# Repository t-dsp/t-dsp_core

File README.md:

# T-DSP Core

**Part of the [T-DSP](https://t-dsp.com) open modular audio platform.**

A compact 4-layer digital backplane for the T-DSP modular ecosystem. Hosts a Teensy 4.1 and ESP32 with USB Audio, MIDI, Ethernet, and TDM expansion headers for connecting T-DSP audio modules.

| | |
|:---:|:---:|
|  |  |
|  |  |

**[View 3D Render Gallery](https://t-dsp.github.io/t-dsp_core/gallery.html)** -- interactive slideshow of all board views

## About T-DSP

T-DSP is an open modular audio platform designed for musicians, engineers, and developers who want powerful digital signal processing in a flexible, hackable format. Built around the [Teensy](https://www.pjrc.com/teensy/) microcontroller and the [Teensy Audio Library](https://www.pjrc.com/teensy/td_libs_Audio.html), T-DSP combines studio-quality audio with a growing library of open-source modules.

Learn more at [t-dsp.com](https://t-dsp.com).

## Overview

The T-DSP Core is a **4-layer digital backplane PCB** hosting a Teensy 4.1 and ESP32 alongside supporting ICs. It provides USB Audio, MIDI, Ethernet, and TDM expansion headers for connecting T-DSP audio modules -- in a more accessible and cost-effective form factor than the 8-layer Desktop Pro.

## Processing

- **Teensy 4.1** -- ARM Cortex-M7 running the Teensy Audio Library for real-time DSP (mixing, effects, synthesis, routing). Also receives USB Audio.
- **ESP32** -- UI controller, WiFi/Bluetooth. Drives the display, buttons, and encoder, and sends commands to the Teensy over serial.

## Connectivity

### Audio I/O
- **3.5mm headphone jack** -- Switchcraft 35RAPC4BV4
- **RCA outputs** -- Stereo analog audio output
- **S/PDIF** -- Digital audio input and output

### USB
- **USB-C DEVICE** -- Power and USB Audio to Teensy with ESD protection
- **USB-A HOST** -- USB host connector

### Networking
- **RJ45 Ethernet** -- Wired network connectivity

### MIDI
- **MIDI input** -- 3.5mm TRS with optical isolation (H11L1)
- **MIDI GPIO** -- Configurable for MIDI in, out, or thru

### Power
- **Dual power input** -- USB-C or external supply via JST-XH header, with TPS22860 power switch for automatic switchover
- **Reverse polarity protection** -- P-channel MOSFET on power inputs
- **Power indicators** -- LED indicators for 5V and 12V rails

### Storage
- **SD card** -- Accessible via Teensy 4.1 built-in SD slot

## Expansion

- **2x TDM expansion headers** (2x10 pin, 2.54mm) -- Connect T-DSP audio modules
  - TDM digital audio bus (BCLK, LRCK, DATA_IN, DATA_OUT, MCLK)
  - I2C control bus (SDA, SCL)
  - Power rails (3.3V, 5V, 12V, GND)
  - Control pins (Held-high, Held-low)
- Modules can be soldered directly or socketed with pin headers
- Multiple modules can be chained on the same TDM bus

## User Interface

- **GPIO header** -- Active-low buttons, rotary encoder, and display connections for tactile UI
- **OLED display header** (128x64, SSD1306) -- Status and menu-driven UI
- **3.2" TFT touchscreen header** (ILI9341) -- Touchscreen UI
- **SK6812 addressable LED header** -- ESP32 and Teensy status indication, plus LED strip control

## Board Design

- **4-layer PCB** -- F.Cu (components/analog), In1.Cu (ground plane), In2.Cu (signal/digital), B.Cu (components/analog)
- **1.6mm board thickness**
- LDO voltage regulation for clean analog power
- Separate analog and digital ground domains
- Buffered digital outputs for reliable module distribution

## Project Files

| Directory | Contents |
|-----------|----------|
| `/3d_models/` | 3D models for PCB components |
| `/documentation/` | Schematic PDF, board images, and reference docs |
| `/lib_fp/` | Custom KiCad footprint libraries |
| `/lib_sch/` | Custom KiCad schematic symbol libraries |
| `/manufacturing/` | CI-generated manufacturing outputs (gerbers, BOM, pick & place) |
| `/panel/` | Panelized board layouts for production |

## Status

This board is under active development.

If you build one, we'd love to hear how it goes -- please open an issue or reach out with your findings.

## Contact

For consulting, custom board design, or commercial licensing inquiries, reach out via [LinkedIn](https://linkedin.com/in/jayshoe).

## License

This project is licensed under the [Creative Commons Attribution-NonCommercial-ShareAlike 4.0 International (CC BY-NC-SA 4.0)](https://creativecommons.org/licenses/by-nc-sa/4.0/).

You are free to share and adapt this work for non-commercial purposes, as long as you give appropriate credit and distribute any derivatives under the same license.

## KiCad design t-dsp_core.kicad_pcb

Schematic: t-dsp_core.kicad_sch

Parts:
C1, C29, C30: 1 uF; C_0603_1608Metric; LCSC C15849
C2, C3, C4, C5, C16, C17, C21, C22, C32, C35, C40: 0.1 uF; C_0603_1608Metric; LCSC C14663
C12, C23, C31, C33, C34, C44: 10 uF; C_0603_1608Metric; LCSC C19702
C15: 100 uF; C_1206_3216Metric_Pad1.33x1.80mm_HandSolder; LCSC C15008
C18, C19, C131, C133, C140, C141, C142, C143, C150, C153: 100nF; C_0603_1608Metric; LCSC C14663
C27, C28: 47uF; C_0805_2012Metric_Pad1.15x1.40mm_HandSolder; LCSC C16780
C41, C42: 10 uF; C_0603_1608Metric; LCSC_MPN CL10A106KP8NNNC
C43: 4.7uF; C_0603_1608Metric; LCSC_MPN CL10A475KO8NNNC
C45: 1 uF; C_0402_1005Metric_Pad0.74x0.62mm_HandSolder; LCSC C29266
C46: 100nF; C_0402_1005Metric_Pad0.74x0.62mm_HandSolder; LCSC C1525
C129: 0.1uF; C_0402_1005Metric_Pad0.74x0.62mm_HandSolder; LCSC C106994
C130, C151: 10uF; C_0603_1608Metric; LCSC C19702
C132, C154: 22uF; C_0805_2012Metric_Pad1.15x1.40mm_HandSolder; LCSC C45783
D2: Diode - 1N4148; D_SOD-123; LCSC C81598
D3: SK6812-EC20; LED_SK6812-EC20_2.0x2.0mm; LCSC C5378721
D4: SK6812-EC20; LED_SK6812-EC20_2.0x2.0mm; LCSC TYPE SMD
D7: SMAJ5.0A; D_SMA; LCSC C78401
FB1: 600Ω@100MHz; BLM15AG601SN1D; LCSC C76884
FL1: BLM18BA121SN1D; LCSC C113012
H1, H2, H3, H4: M3 NPTH 3.2mm; MountingHole_3.2mm_M3
IC1: Logic Level Shifter - 74HCT2G125DC,125; SOP50P310X100-8N; LCSC C547558
J1: J_PWR; PinHeader_2x05_P2.54mm_Vertical
J2: J_TDM; PinHeader_2x14_P2.54mm_Vertical
J3: J_T; PinHeader_2x12_P2.54mm_Vertical
J4: J_USB; PinHeader_2x05_P2.54mm_Vertical
J5: J_MIDI; PinHeader_2x04_P2.54mm_Vertical
J7: J_SAI2; PinHeader_2x06_P2.54mm_Vertical
J8: J_S3; PinHeader_2x17_P2.54mm_Vertical
J11: J_LED; PinHeader_1x05_P2.54mm_Vertical
J12: J_ETH; PinHeader_2x04_P2.54mm_Vertical
J13: u.FL DNP (IDC767 ext-antenna build only); U.FL_Hirose_U.FL-R-SMT-1_Vertical
JP1: SJ bridged; SolderJumper-2_P1.3mm_Bridged_Pad1.0x1.5mm
L1: 3.3uH; L_Taiyo-Yuden_NR-40xx; LCSC C92960
PU_EN1: JUMPER; SolderJumper-2_Open_Pad0.5x1.0mm_PU; not fitted
Q1: AO3401A; SOT-23; LCSC C15127
R3, R4, R5, R6, R7, R9, R40, R41, R42, R43, R44, R45, R46, R47, R52, R55, R56, R75, R76, R81, R89, R90, R91, R92, R93, R94, R95, R96, R97, R98, R99, R100, R101: 33 ohm; R_0603_1608Metric; LCSC C23140
R8, R32, R34, R36, R37, R38, R39: 220 ohm; R_0603_1608Metric; LCSC C22962
R11, R19, R53, R54, R73, R74, R86, R87, R88: 10k; R_0603_1608Metric; LCSC C25804
R12, R15, R31, R35, R59, R60, R77, R80, R83, R84: 0 ohm; R_0603_1608Metric; LCSC C21189
R13, R14, R16, R17, R67, R68: 2.2k ohm; R_0603_1608Metric; LCSC C4190
R33: 1.5k ohm; R_0603_1608Metric; LCSC C22843
R57: 33.0 k; R_0603_1608Metric; LCSC_MPN 0603WAF3302T5E
R58: 300 ohm; R_0603_1608Metric; LCSC_MPN 0603WAF3000T5E
R61: 33 ohm; R_0603_1608Metric; LCSC_MPN 0603WAF330JT5E
R66, R72: 100k; R_0603_1608Metric; LCSC C25803
R78, R79, R82, R85: 0 ohm DNP; R_0603_1608Metric; LCSC C21189
T108, T109, T110, T111: Tab; not fitted
U1: Teensy 4.1 - DEVKIT; Teensy41; LCSC CONSIGN; not fitted
U4: Optoisolators - H11L1SM - 6-SMD, Gull Wing; IC_H11L1SM; LCSC C899473
U5: SN74LVC541APWR; TSSOP-20_4.4x6.5mm_P0.65mm; LCSC C113281
U6, U7, U20: SN74LVC2G125DCTR; SOP65P400X130-8N; LCSC C206035
U9: Dual Buffer - 74HCT2G17GW,125; SOT-363_SC-70-6; LCSC C547568
U11: Dual Buffer - SN74LVC2G125DCTR; SOP65P400X130-8N; LCSC C206035
U13: ESP32-S3-WROOM-1-N16R8; ESP32-S3-WROOM-1; LCSC C2913202
U15: LT3045EMSE#TRPBF; MSOP-12-1EP_3x4.039mm_P0.65mm_EP1.651x2.845mm; LCSC C666577
U19: SN74LVC257APWR; TSSOP-16_4.4x5mm_P0.65mm; LCSC C205921
U21: SN74LVC244APWR; TSSOP-20_4.4x6.5mm_P0.65mm; LCSC C7668
U22: IDC777-1; LCSC CONSIGN
U23: SN74LVC138APWR; TSSOP-16_4.4x5mm_P0.65mm; LCSC C485077
U24: AP63203WU; TSOT-23-6; LCSC C780769
Y1: 24.576MHz; Oscillator_SMD_Abracon_ASE-4Pin_3.2x2.5mm; LCSC C6159263

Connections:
3.3V: C17.1, C18.1, C19.1, C27.1, C30.1, C40.1, C42.1, C129.1, FB1.1, J1.7, PU_EN1.1, R11.1, R12.2, R15.2, R19.1, R31.2, R74.1, R78.2, R80.2, R83.2, R85.2, U5.20 (VCC), U6.8 (VCC), U7.7 (~2OE), U7.8 (VCC), U11.8 (VCC), U15.10 (OUTS), U15.11 (OUT), U15.12 (OUT)
3.3V_DIG: C132.1, C133.1, C140.1, C141.1, C142.1, C143.1, C150.1, C151.1, C154.1, J1.8, J7.11, L1.2, R73.1, R86.1, R87.1, U13.2 (3V3), U19.16 (VCC), U20.8 (VCC), U21.20 (VCC), U22.30 (VBAT_SENSE), U22.31 (VBAT), U22.32 (VDD_PADS), U23.6 (E3), U23.16 (VCC), U24.1 (FB)
5V: C15.1, C22.1, C23.1, C28.1, C29.1, C34.1, C35.1, C130.1, C131.1, D3.2 (VDD), D4.2 (VDD), FL1.1, IC1.8 (VCC), J1.5, J1.6, J7.12, J8.12, J11.5, Q1.2 (S), R35.2, R37.2, R39.2, R66.1, U1.48 (VIN), U24.3 (IN)
5V_IN: C12.1, D7.1 (K), J1.1, J1.2, Q1.3 (D)
6_OUT1D: R4.2, U5.9 (A7)
6_OUT1D+: J2.16, R47.2
7_OUT1A: R3.2, U5.5 (A3)
7_OUT1A+: J2.15, R46.2
8_IN1: J2.17, U11.2 (1A)
8_IN1+: R55.2, U1.10 (8_TX2_IN1)
9_OUT1C_INPUT: J2.18, R81.2, U11.5 (2A)
9_OUT1C_INPUT+: R56.2, U1.11 (9_OUT1C), U7.2 (1A)
32_OUT1B: J2.27, R75.2, U6.5 (2A)
/OUT1B_MCU: R5.2, R76.2, U1.24 (32_OUT1B), U6.2 (1A)
/OUT1B_OE_IN: R79.1, R80.1, U6.7 (~2OE)
/OUT1B_OE_OUT: R77.1, R78.1, U6.1 (~1OE)
/OUT1C_OE_IN: R84.1, R85.1, U11.7 (~2OE)
/OUT1C_OE_OUT: R82.1, R83.1, U7.1 (~1OE)
/S3_IO43_TXD0: J8.30, U1.20 (28_RX7), U13.37 (TXD0)
/S3_IO44_RXD0: J8.29, U1.21 (29_TX7), U13.36 (RXD0)
/TDM1_BCLK_B: R44.1, U5.16 (Y2)
/TDM1_DOUT_B: R46.1, U5.15 (Y3)
/TDM1_LRCK_B: R42.1, U5.18 (Y0)
/TDM1_MCLK_B: R41.1, U5.17 (Y1)
/TDM2_BCLK_B: R45.1, U5.12 (Y6)
/TDM2_DOUT_B: R47.1, U5.11 (Y7)
/TDM2_LRCK_B: R43.1, U5.14 (Y4)
/TDM2_MCLK_B: R40.1, U5.13 (Y5)
/TDM2_OE: JP1.1, R74.2, U5.19 (G2)
AUX_I2S_BCK: J7.5, R95.2, U21.2 (I0a)
AUX_I2S_DIN: J7.9, U20.2 (1A), U20.5 (2A)
AUX_I2S_DOUT: J7.10, R94.2, R98.2
AUX_I2S_LRCK: J7.7, R96.2, U21.4 (I1a)
AUX_I2S_MCLK: J7.3, R97.2, R101.2
BCLK1: R6.2, U5.4 (A2), U5.8 (A6)
BCLK1+TDM1: J2.7, R44.2
BCLK1+TDM2: J2.8, R45.2
BT_BCK: U19.2 (I0a), U22.53 (PCM_CLK)
BT_EXT_RF: J13.1 (In), U22.57 (EXT_RF)
BT_LRCK: U19.5 (I0b), U22.52 (PCM_SYNC)
BT_RST: U13.33 (IO40), U22.36 (~RST)
BT_SDATA: U19.14 (I0c), U22.54 (PCM_OUT)
BT_SYS_CTRL: R72.1, U13.34 (IO41), U22.13 (SYS_CTRL)
BT_UART_RX: U13.15 (IO3), U22.39 (UART_RX)
BT_UART_TX: U13.9 (IO16), U22.38 (UART_TX)
EN_3V3_DIG: R66.2, U24.2 (EN)
ESP32_LED+: D4.1 (DIN), IC1.6 (1Y)
ESP32_LED_OUT: D4.3 (DOUT), J11.4
ETH_LED: J12.7
ETH_R+: J12.1
ETH_R-: J12.2
ETH_T+: J12.5
ETH_T-: J12.6
GND: C1.2, C2.2, C3.2, C4.2, C5.2, C12.2, C15.2, C16.1, C17.2, C18.2, C19.2, C21.1, C22.2, C23.2, C27.2, C28.2, C29.2, C30.2, C31.2, C32.2, C33.2, C34.2, C35.2, C40.2, C41.2, C42.2, C43.2, C44.2, C45.2, C46.2, C129.2, C130.2, C131.2, C132.2, C133.2, C140.2, C141.2, C142.2, C143.2, C150.2, C151.2, C154.2, D3.4 (GND), D4.4 (GND), D7.2 (A), IC1.1 (~1OE), IC1.4 (GND), IC1.7 (~2OE), J1.3, J1.4, J1.10, J2.1, J2.2, J2.5, J2.6, J2.9, J2.10, J2.13, J2.14, J2.19, J2.20, J2.25, J2.26, J2.28, J3.1, J3.2, J3.5, J3.6, J3.15, J3.16, J3.21, J3.22, J3.23, J3.24, J4.1, J4.2, J4.7, J4.8, J4.10, J5.7, J5.8, J7.1, J7.2, J7.4, J7.6, J7.8, J8.1, J8.2, J8.8, J8.11, J8.16, J8.21, J8.22, J8.27, J8.28, J8.33, J8.34, J11.1, J11.3, J12.3, J12.4, J12.8, J13.2 (Ext), JP1.2, Q1.1 (G), R33.1, R53.2, R54.1, R57.1, R58.1, R60.2, R72.2, R77.2, R79.2, R82.2, R84.2, R88.2, U1.1 (GND), U1.34 (GND), U1.47 (GND), U1.52 (GND), U1.58 (GND), U1.59 (GND), U5.1 (G1), U5.10 (GND), U6.4 (GND), U7.4 (GND), U7.5 (2A), U9.2 (GND), U11.1 (~1OE), U11.4 (GND), U13.1 (GND), U13.40 (GND), U13.41 (GND), U15.9 (GND), U15.13 (GND), U19.8 (GND), U19.10 (I1d), U19.11 (I0d), U20.4 (GND), U21.10 (GND), U22.1 (GND), U22.12 (GND), U22.18 (GND), U22.19 (GND), U22.21 (GND), U22.22 (GND), U22.27 (GND), U22.34 (GND), U22.35 (GND), U22.41 (GND), U22.51 (GND), U22.56 (GND), U22.58 (GND), U22.59 (GND), U22.60 (GND), U23.3 (A2), U23.4 (E1), U23.5 (E2), U23.8 (GND), U24.4 (GND), Y1.2 (GND)
HOST_5V: C1.1, C33.1, J4.9, U1.55 (5V)
HOST_D1+: J4.5, U1.57 (D+)
HOST_D1-: J4.3, U1.56 (D-)
LRCK1: R9.2, U5.2 (A0), U5.6 (A4)
LRCK1+TDM1: J2.11, R42.2
LRCK1+TDM2: J2.12, R43.2
MCLK1: R7.2, R61.2, U5.3 (A1), U5.7 (A5)
MCLK1+TDM1: J2.3, R41.2
MCLK1+TDM2: J2.4, R40.2
MIDI_IN_4: J5.1, R32.1
MIDI_IN_5: D2.2 (A), J5.2, U4.2
MIDI_OUT_4: J5.3, R39.1
MIDI_OUT_5: J5.4, R38.1
MIDI_RX: R34.1, U1.2 (0_RX1_CRX2_CS1), U4.4, U9.3
MIDI_THRU_4: J5.5, R37.1
MIDI_THRU_5: J5.6, R36.1
MIDI_TX_T: U1.3 (1_TX1_CTX2_MISO1), U9.1
unnamed: C16.2, R31.1, R34.2, U4.6
unnamed: C31.1, C32.1
unnamed: D2.1 (K), R32.2, U4.1
unnamed: PU_EN1.2, R67.1, R68.1
unnamed: R12.1, R13.2, R14.2
unnamed: R15.1, R16.2, R17.2
unnamed: R33.2, U4.5
unnamed: R36.2, U9.4
unnamed: R38.2, U9.6
unnamed: R4.1, U1.8 (6_OUT1D)
unnamed: R3.1, U1.9 (7_RX2_OUT1A)
unnamed: R9.1, U1.42 (20_A6_TX5_LRCLK1)
unnamed: R6.1, U1.43 (21_A7_RX5_BCLK1)
unnamed: R7.1, U1.45 (23_A9_CRX1_MCLK1)
unnamed: R52.1, U1.23 (31_CTX3)
unnamed: R8.2, U1.33 (41_A17)
unnamed: R75.1, U6.6 (1Y)
unnamed: R76.1, U6.3 (2Y)
unnamed: R81.1, U7.6 (1Y)
unnamed: C21.2, R35.1, U9.5 (VCC)
unnamed: R55.1, U11.6 (1Y)
unnamed: R56.1, U11.3 (2Y)
unnamed: C41.1, FL1.2, U15.1 (IN), U15.2 (IN), U15.3 (IN), U15.4 (EN/UV)
unnamed: R58.2, U15.6 (ILIM)
unnamed: C43.1, R57.2, U15.8 (SET)
unnamed: R89.1, U19.4 (Za)
unnamed: R90.1, U19.7 (Zb)
unnamed: R91.1, U19.12 (Zc)
unnamed: R99.1, U20.6 (1Y)
unnamed: R100.1, U20.3 (2Y)
unnamed: R92.1, U21.18 (O0a)
unnamed: R95.1, U21.9 (O0b)
unnamed: R93.1, U21.16 (O1a)
unnamed: R96.1, U21.7 (O1b)
unnamed: R101.1, U21.14 (O2a)
unnamed: R97.1, U21.5 (O2b)
unnamed: R94.1, U21.12 (O3a)
unnamed: R98.1, U21.3 (O3b)
unnamed: C153.1, U24.6 (BST)
unnamed: C153.2, L1.1, U24.5 (SW)
unnamed: R61.1, Y1.3 (Out)
unnamed: R59.2, R60.1, Y1.1 (Standby)
unnamed: C44.1, C45.1, C46.1, FB1.2, R59.1, Y1.4 (VDD)
S3_EN: C4.1, J8.3, R73.2, U1.29 (37_CS), U13.3 (EN)
S3_I2S_BCK: U13.6 (IO6), U19.3 (I1a)
S3_I2S_DOUT: U13.7 (IO7), U19.13 (I1c)
S3_I2S_LRCK: U13.4 (IO4), U19.6 (I1b)
S3_IO0_BOOT: C5.1, J8.23, U1.28 (36_CS), U13.27 (IO0)
S3_IO1: J8.32, U13.39 (IO1)
S3_IO2: J8.31, U13.38 (IO2)
S3_IO5: J8.4, U13.5 (IO5)
S3_IO8: J8.7, U13.12 (IO8)
S3_IO9: J8.13, U13.17 (IO9)
S3_IO10: J8.14, U13.18 (IO10)
S3_IO11: J8.15, U13.19 (IO11)
S3_IO12_SPI_MISO: R53.1, U1.14 (12_MISO_MQSL), U13.20 (IO12)
S3_IO13_SPI_MOSI: U1.13 (11_MOSI_CTX1), U13.21 (IO13)
S3_IO14_SPI_SCK: U1.35 (13_SCK_LED), U13.22 (IO14)
S3_IO15: J8.5, U13.8 (IO15)
S3_IO17_SPI_CS: R19.2, U1.12 (10_CS_MQSR), U13.10 (IO17)
S3_IO18: J8.6, U13.11 (IO18)
S3_IO21_SDA: J8.17, R67.2, U13.23 (IO21)
S3_IO38: J8.24, U13.31 (IO38)
S3_IO39: J8.25, U13.32 (IO39)
S3_IO42: J8.26, U13.35 (IO42)
S3_IO45: J8.20, U13.26 (IO45)
S3_IO46_LED: IC1.2 (1A), U13.16 (IO46)
S3_IO47_SCL: J8.18, R68.2, U13.24 (IO47)
S3_IO48: J8.19, U13.25 (IO48)
S3_USB_DN: J8.9, U13.13 (USB_D-)
S3_USB_DP: J8.10, U13.14 (USB_D+)
SAI2_BCLK: R89.2, R92.2, U1.6 (4_BCLK2), U21.11 (I0b)
SAI2_IN: R91.2, R99.2, R100.2, U1.7 (5_IN2)
SAI2_LRCLK: R90.2, R93.2, U1.5 (3_LRCLK2), U21.13 (I1b)
SAI2_MCLK: U1.25 (33_MCLK2), U21.6 (I2a), U21.15 (I2b)
SAI2_MODE0: R86.2, U1.18 (26_A12_MOSI1), U23.1 (A0)
SAI2_MODE1: R87.2, U1.19 (27_A13_SCK1), U23.2 (A1)
SAI2_OUT: U1.4 (2_OUT2), U21.8 (I3a), U21.17 (I3b)
SAI2_SEL: R88.1, U1.44 (22_A8_CTX1), U19.1 (S)
SAI2_nOE_HDR: U20.1 (~1OE), U21.1 (OEa), U23.14 (O1)
SAI2_nOE_INT: U19.15 (OE), U23.15 (O0)
SAI2_nOE_OUT: U20.7 (~2OE), U21.19 (OEb), U23.13 (O2)
T14_SPDIF_OUT: J3.3, U1.36 (14_A0_TX3_SPDIF_OUT)
T15_SPDIF_IN: J3.4, U1.37 (15_A1_RX3_SPDIF_IN)
T16_SCL1: J2.24, R17.1, U1.38 (16_A2_RX4_SCL1)
T17_SDA1: J2.22, R16.1, U1.39 (17_A3_TX4_SDA1)
T18_SDA0: J2.21, R14.1, U1.40 (18_A4_SDA)
T19_SCL0: J2.23, R13.1, U1.41 (19_A5_SCL)
T24: J3.13, U1.16 (24_A10_TX6_SCL2)
T25: J3.14, U1.17 (25_A11_RX6_SDA2)
T30_CRX3: J3.7, U1.22 (30_CRX3)
T31_CTX3: J3.8, R52.2
T32_OUT1B: J3.20, R5.1
T34_RX8: J3.10, R54.2, U1.26 (34_RX8)
T35_TX8: J3.9, R11.2, U1.27 (35_TX8)
T38: J3.17, U1.30 (38_CS1_IN1)
T39: J3.18, U1.31 (39_MISO1_OUT1A)
T40: J3.19, U1.32 (40_A16)
TEENSY_LED: IC1.5 (2A), R8.1
TEENSY_LED+: D3.1 (DIN), IC1.3 (2Y)
TEENSY_LED_OUT: D3.3 (DOUT), J11.2
T_ON_OFF: C3.1, J3.12, U1.54 (ON_OFF)
T_PROGRAM: C2.1, J3.11, U1.53 (PROGRAM)
T_USB_DN: J4.4, U1.66 (D-)
T_USB_DP: J4.6, U1.67 (D+)
V_BAT: J1.9, U1.50 (VBAT)

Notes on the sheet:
SK6812 STATUS LEDs - 5V level shifter IC1, chain continues to header (TEENSY_LED_OUT / ESP32_LED_OUT)
5V INPUT MUX - TPS2116: VIN1 = header 5V_IN (priority), VIN2 = Teensy VUSB (cut the VUSB-VIN pad on the Teensy). VOUT = 5V rail -> Teensy VIN, buck, LT3045
MCLK SOURCE - Y1 24.576 MHz (512 fs) feeds MCLK1 via R61; Teensy pin 23 reaches MCLK1 via R7. EXTERNAL-MCLK BUILD: populate R59 (Y1 on), DNP R60; firmware must set IOMUXC_GPR_GPR1 SAI1_MCLK_DIR=0 so pin 23 is an input. DEFAULT BUILD (no firmware yet): populate R60 (Y1 standby), DNP R59; Teensy driv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
TEENSY 4.1 - series terminations, SPI link to S3, CAN3, program lines
Header net naming: functions keep function names (TDM, SPDIF, USB, MIDI, DMX, LED, power); raw GPIO is named by MCU pin: T<n> = Teensy 4.1 pin n,\nS3_IO<n> = ESP32-S3 GPIO n; an optional core function rides as a suffix (T14_SPDIF_OUT, T35_TX8, T18_SDA0, S3_IO43_TXD0, S3_IO47_SCL).\nSimple backplane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
Interlock U23 (SAI2_MODE1:MODE0, pulled up = 11 = all off). 00 internal: U19 mux (SAI2_SEL 0 = IDC777, 1 = ESP32-S3) drives BCLK/LRCLK/IN, Teensy SAI2 slave.
https://electronics.stackexchange.com/questions/310899/midi-out-thru-circuit-questions
01 header master (core slave): U21 group 1 passes AUX BCLK/LRCLK in and MCLK/DOUT out, U20 gate 1 passes AUX DIN. 10 core master: U21 group 2 drives AUX BCLK/LRCLK/MCLK/DOUT, U20 gate 2 passes AUX DIN.
J_ETH: Teensy 4.1 Ethernet pads 60-65 (R+ R- T+ T- LED GND, 2 mm 2x3 on the Teensy bottom).\nPENDING: change U1 to project_sch:Teensy4.1 in eeschema, label pins 60=ETH_R+ 61=ETH_LED 62=ETH_T- 63=ETH_T+ 64=GND 65=ETH_R-,\nand restore pads 60-65 in Teensy41_mod3 (they exist in Teensy41.kicad_mod). Ma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
ESP32-S3 - WROOM-1-N16R2 (PCB antenna). IO4/6/7 = I2S master -> mux, IO16/IO35 = BT UART, IO46 = LED chain, IO19/20 = USB -> header, UART0 -> Teensy Serial7 + header
BLUETOOTH SINK - IDC777-1 (CONSIGNED part). I2S master into mux U21. UART to S3, RST/SYS_CTRL from SRC GPO1/GPO2, R72 = SYS_CTRL pulldown. Antenna end at a 100 mm board edge, copper-free keepout all layers.
SAI2 AUX INPUT BLOCK (stage 10y). One asynchronous I2S source at a time into Teensy SAI2; sample-rate conversion is done in Teensy software (no hardware SRC).
Low-Jitter Audio Clock
3.3V RAIL DECOUPLING
U13 = ESP32-S3-WROOM-1-N16R8 (16 MB flash + 8 MB OCTAL PSRAM, needed for Spotify/cspot stream buffering).\nOctal PSRAM owns IO35/IO36/IO37 -> those module pins are NC. BT UART RX therefore uses IO3 (not IO35).\nDo not substitute an R2 (quad) module without re-checking: R2 frees IO35-37 but 2 MB PSR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
3.3V_DIG BUCK - AP63203 2 A (S3, BT, SRC, mux, isolator) + 5V input decoupling. EN pulled up by R66.
MIDI IN
TDM BUS BUFFERS - Teensy I2S1 -> TDM1 / TDM2 (74LVC2G125). Slave-clock option: buffer ~OE + bypass jumpers, see change-map section 8
MIDI THROUGH
MIDI
EDGE HEADERS - J1/J2 Teensy domain, J3/J4 S3 domain. Two 2x22 side by side per 60.96 mm edge. Pin map: documentation/core-spin2-change-map.md section 13. RESERVED pins carry no-connect flags.
Every driver reaches the shared SAI2_* / AUX_I2S_* nets through its own 33 R; only one group is ever enabled. Teensy pins: BCLK2 = 4, LRCLK2 = 3, IN2 = 5, OUT2 = 2, MCLK2 = 33, SEL = 44 (T22), MODE0 = 18 (T26), MODE1 = 19 (T27).
U1 Teensy 4.1 memory: fit 2x APS6404L-3SQR-SN (8 MB PSRAM each, 16 MB total, EXTMEM) on the Teensy's own bottom-side SOIC-8 pads\nfor loop recording, echo and reverb buffers. Optional W25Q128 QSPI flash on the second pad if 8 MB PSRAM + flash is preferred.\nPCB rule: no parts or pads on the core to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
MIDI circuit from TeensyMIDIAudio project.
3.3V ANALOG RAIL - LT3045 500 mA ultra-low-noise LDO (SET 33k = 3.3 V). Feeds buffers, pull-ups, header 3.3V pins. Teensy 3V3 is NOT connected to this rail.
MIDI OUT
J13 u.FL: DNP with the IDC777-1 (chip antenna). Fit J13 and populate U22 as IDC767 (same 60-pad LGA, pad 57 = EXT_RF) for an external antenna.\nPCB: 50 ohm CPW from pad 57 to J13, GND pads 56/58 either side, ground vias every 1-2 mm, keep it short, no matching network (IDC767-DTS-V003 p.8).
MOUNTING HOLES / PANEL TABS
MIDI IN / OUT / THRU - H11L1 opto + 74HCT2G17 buffer. Jack-level signals go to header J2 (MIDI_IN/OUT/THRU_4/5)

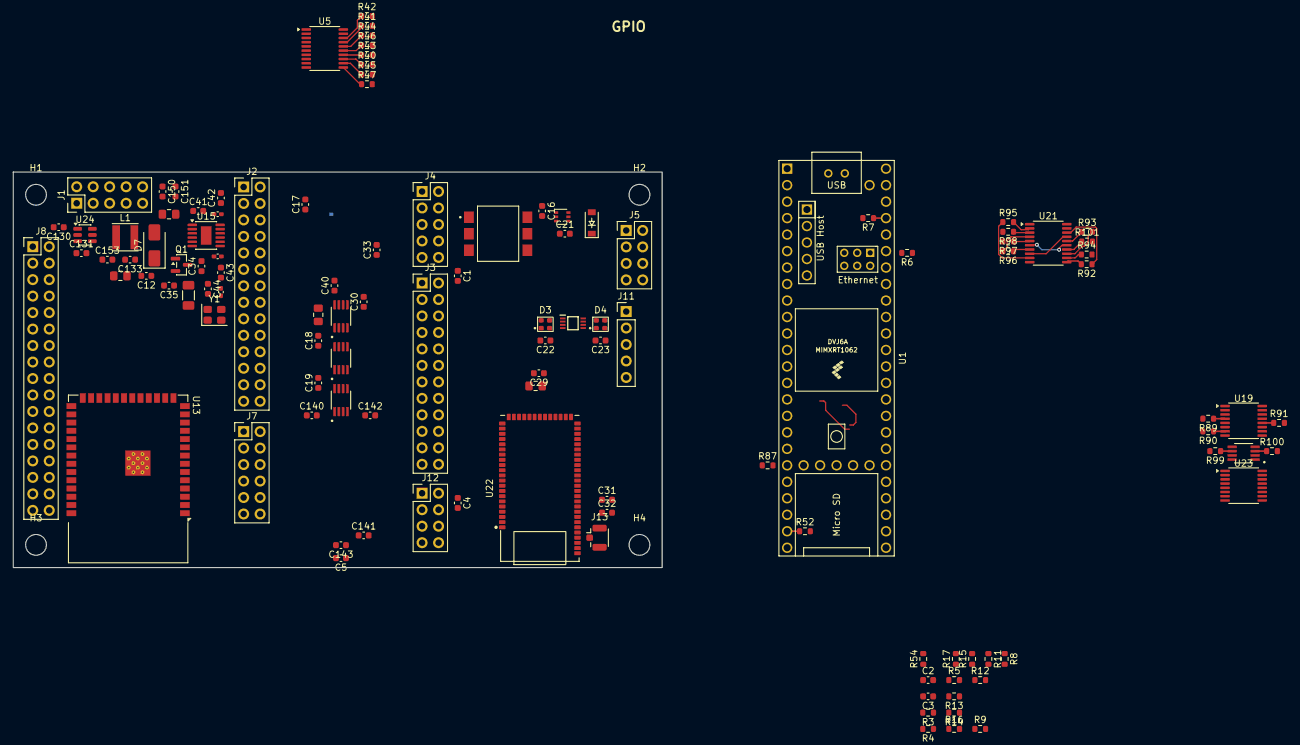
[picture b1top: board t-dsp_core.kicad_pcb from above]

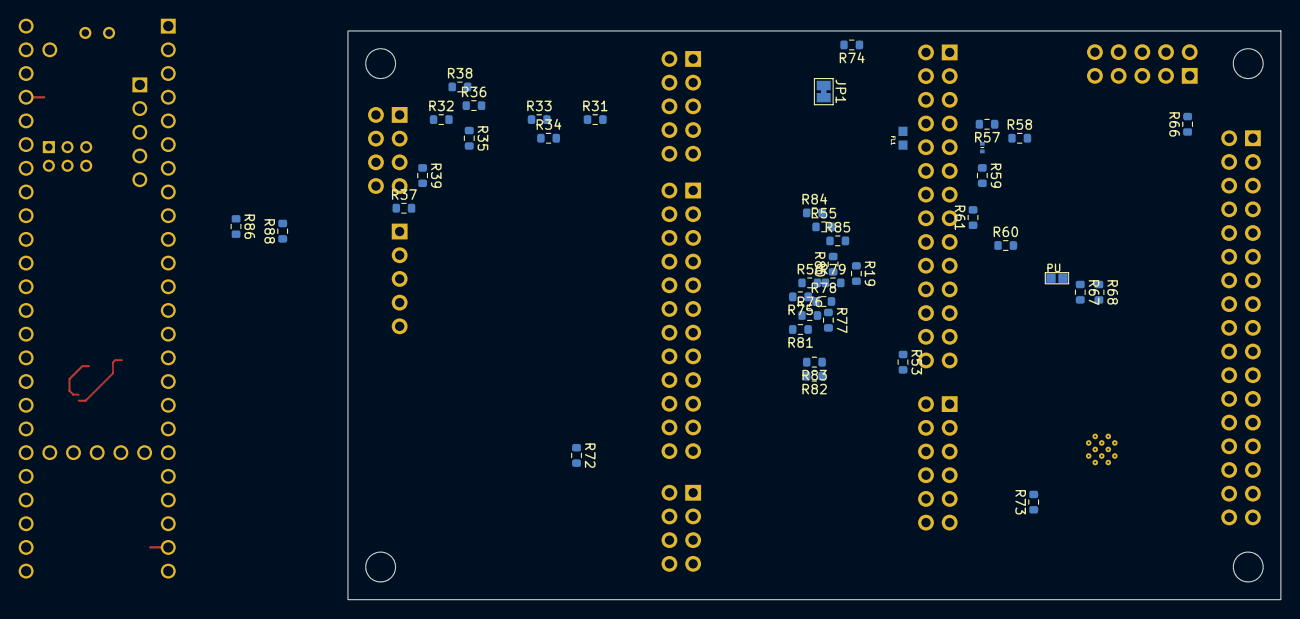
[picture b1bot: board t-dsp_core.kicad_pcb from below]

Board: 4 copper layers, 100.0 x 61.0 mm, 164 parts (41 on the bottom side), 172 nets.

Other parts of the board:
board_outline2: board_outline; audio_project_board_outline_100x60.96

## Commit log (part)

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2026-02-28 Initial commit: T-DSP Core 4-layer audio backplane
    KiCad project for the T-DSP Core — a 4-layer audio backplane hosting
    Teensy 4.1, ESP32, and T-DSP TAC5212 codec module. Derived from the
    T-DSP Desktop Pro with a simplified 4-layer stackup for lower cost.
2026-02-28 Fix CI: rename project references and update to 4-layer stackup
    - Update manufacturing.yml: all t-dsp_desktop_pro → t-dsp_core
    - Update .kibot.yaml: project name, 4-layer board comment, remove In3-In6
    layers from gerbers and pcb_pdf (4-layer has only F.Cu, In1.Cu, In2.Cu, B.Cu)
    - Update gallery.html: title, GitHub link, render filename prefix
2026-02-28 Fix README: digital only backplane, remove TAC5212 references
2026-02-28 Add 3D render gallery to README
